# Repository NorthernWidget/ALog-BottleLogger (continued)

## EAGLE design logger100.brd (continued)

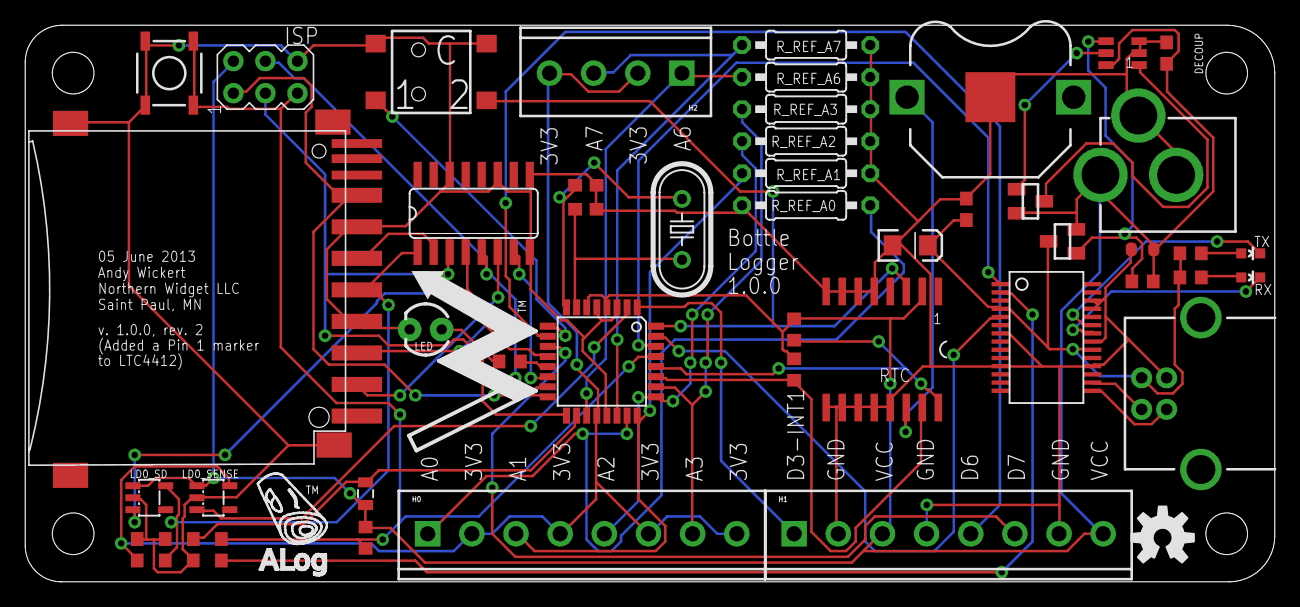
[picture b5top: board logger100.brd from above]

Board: 2 copper layers, 99.0 x 44.1 mm, 54 parts (0 on the bottom side), 46 nets.

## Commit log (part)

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2013-09-11 Create LICENSE.html: CC-BY-SA
2013-09-11 Adding version 0.6.6
2013-09-11 Adding version 1.0.0 files to the master branch
2016-04-27 Next generation: breaking out more pins
2016-04-27 exposed interfaces, button update, board layout
    (1) Exposed SPI, I2C, and UART interfaces
    (2) Added 1K resistors to UART to allow switching away from the computer
    (3) Updated the buttons to PTH (higher button: RESET), PTH DPDT b/c of
    availability (LOG NOW)
    (4) Reworked the board layout to keep the same form factor while adding
    many new screw terminals (and keeping the 3.5 mm spacing)
2016-04-27 Github new standard Eagle-specific
2016-04-27 10nF chip caps for analog, following Gerhard Oberforcher
2016-04-27 a big mess of getting a new FTDI chip
2016-04-28 Added diode OR, not connected yet
2016-04-28 New FTDI chip, power-saving clock circuits (h/t Gerhard), with Chad Sandell
2016-04-28 routed board with clock power-save and new FTDI
2016-04-28 Uniform MOSFETs; diode connection fix
2016-04-29 ALog 1.1 complete
2016-04-29 Improved board, modified and consolidated some components
2016-04-29 Rmv via at screw hole
2016-04-29 Final BoM for ALog 1.1 order
2016-05-07 Return to classic FTDI USB/serial
2016-05-07 Keep a live version of Logger 1.1.0 (new FTDI)
2016-05-17 can not get this to autoroute
2016-05-17 removing the ._## junk eagle files
2016-05-17 Routed board, ground fills and minimized timing device distances
2016-05-18 replace logger with logger_Chad
2016-05-18 remove logger_Chad files, changed to logger
2016-05-20 Added 5V boost from VCC to board
2016-05-24 Route EN pin to tie into 3.3V digital pin (D6 I think)
2016-05-25 5V pin on both sides of board instead of duel ground pins on one side
2016-06-07 Clock power for pull-ups on I2C
2016-06-07 Vcl attached to clock power and communication
2016-06-07 Straighten traces
2016-06-07 Charge pump
2016-06-08 Routed charge pump and gerbers
2016-07-22 Logger2 and logger3, in progress
2016-07-25 fully routed and ready for check
2016-07-28 Updated component packaging
2016-07-28 Updated BOM and board layout with cheaper and smaller component packages
2016-08-01 33pF decoupling on USB data; Rx Tx LED flip
2016-08-09 Fixed misrouted trace
2016-08-09 Update date and version
2016-08-31 Latest design files and board lable fix
2016-09-01 Moved MOSFETs away from clock backup battery
2016-09-16 Final files for V2.0!
2016-09-26 updated schematic layout, added frames
2016-10-06 Added JST connector option to logger, started 2G communication
2016-10-20 BOM additions for ARM chip Alog
2016-10-28 change 3V3 power supply with jumpers, routing needs finishing
2016-10-29 Routed and ready for Wickert check of approval
2016-10-30 Added version number
2016-10-30 Connected VDD to VCL
2016-10-30 Version number visible
2016-10-30 Rerouted with VDD linked to RTC and SD; updated silk labels
2016-10-31 Updates from change to duel 3.3V regulator
2016-10-31 BOM updates from change to duel 3.3V regulator
2016-10-31 removed via under ground pad and fixed 1 airwire
2016-11-23 Old board schematics and diagrams
2016-11-23 Rename folder
2016-11-23 4-page schematic, for publication
2016-11-23 v2.0
2016-11-23 Remove old/other versions
2016-11-23 Logger 2.0 layout, no fill shown, from Eagle
2016-12-20 clean up BOM document
2016-12-20 4412 routing fix and silkscreen gerber fix
2016-12-29 Fix device usage column
2016-12-29 Remove ALog v1.0.0 BoM
2016-12-30 fixed Miso Mosi Silk Screen labels
2017-01-05 Routed new layout, no precision 3V3
2017-01-06 increased pad sizes for 3V3
2017-01-08 Relegating to archive
2017-01-08 5V5 --> 5V
2017-01-09 Create custom pads for 3V3 output voltage chip
2017-01-09 Updated Gerbers
2017-01-22 v2.0-beta silk updates
2017-01-25 Increased pad length for capacitor array
2017-01-30 Switch pins to PWM; need to update software!
2017-01-30 Unnecessary... or at least, so I think.
2017-01-31 Silk
2017-01-31 Silk on proper side
2017-01-31 All pins properly marked; GND plane vias added
2017-01-31 Updated to newer Eagle version
2017-01-31 Safer 5.0V max suggested on silkscreen
2017-01-31 changes to vias
2017-02-04 Smaller back silk -- doesn't overlap through-hole components
2017-02-07 Silk updates for Gerbers
2017-02-07 Remove archives of stored Gerbers
2017-02-07 Old PnP file
2017-02-07 Updated Gerbers: version 2.0.0
2017-02-07 Pick-and-place files
2017-02-08 Visualize the Gerber with gerbv
2017-02-08 Upload to PCB fab house
2017-03-01 Organize silkscreen layers
2017-03-01 Moved 4050 up to increase label visibility, work in progress
2017-03-01 Finished reroute for silk screen label optimization
2017-03-01 Swap swp files
2017-03-08 Simplify I2C pull-ups: no more shorts
2017-03-11 Routed airwires; created larger ground planes
2017-03-11 One more airewire; just TX to go
2017-03-11 SMD LED and Crystal, with I2C pullup short fix
2017-03-11 Silk date update, Route GND, DRC and clearance
2017-03-19 changed pads on capacitor array's, ready for prime time? Check crystal pad.
2017-03-19 chaged pads on 3V3 chip, V2.1.0 ready
2017-03-20 Silkscreen updates
2017-03-21 silk screen updates
2017-03-21 Logo now properly on back silk layer
2017-03-21 Fix logger board outline
2017-03-22 V2.1.0 gerber files
2017-03-22 Gerber update
2017-03-23 SMD USB (micro-B), barrel jack, and battery holder; tentative SMD 1x6 header blocks
2017-03-23 Barrel jack not protruding from board, and fully re-routed
2017-03-31 MOSFET level shifter for SPI, parts for I2C
2017-03-31 All airwires routed; parts for I2C level shifter remain
2017-03-31 Level shifting for I2C
2017-03-31 Rollback to pre-MOSFET-re-addition
2017-04-01 Restore SDA and SCL level shifter; 3V3 output from board
2017-04-01 Note 3V3 SDA, SCL on silk layer
2017-04-07 through hole and surface mount design in progress
2017-04-10 Surface mount reference resistor sockets need to be centered, removing for now
2017-04-10 Removed Surface mount ref resistor headers and changed USB connector
2017-04-10 Updated silk; updates to 'awickert.lbr' messed up voltage switcher
2017-04-10 Fixed accedental change to 4412 chip
2017-05-10 Graphical user's layout for quick reference
2017-05-10 Additional layouts with smaller file sizes
2017-05-11 Larger PNGs: sufficient resolution
2017-05-11 Diagrams, bulletted text
2017-05-11 transparency update
2017-05-11 Data logger unannotated: ALog BottleLogger v2.2.0
2017-05-11 Update to standard image include
2017-05-11 export PNG tweak
2017-05-11 No more shadow of v2.0.0 behind
2017-05-16 changed micro USB to 10118194-0001LF
2017-05-17 lengthened micro USB pads
2017-06-06 empty
2017-06-06 CC-BY-SA 3.0
2017-06-06 Naming consistency with other boards: no longer the only "logger"!
2017-07-01 ALog logo on back silk; no Northern Widget
2017-07-02 Schematic and layout
2017-07-19 Major revision, 1284P 16 channel 16-bit ADC
2017-07-21 Work in progress
2017-07-24 some progress
2017-07-27 more progress
2017-08-01 progress
2017-08-22 latest design files
2017-08-24 4.75 inches long, reference voltages broken out
2017-08-24 fully routed, looking for review
2017-08-24 Add 10K pull downs on mosphets for external controls
2017-08-30 Fixed 5V control and a few other things, fully routed and ready for review
2017-09-05 update gerber files
2017-09-05 add .dri and .gpi files
2017-09-21 Changed cap sizes on 10 and 22 uF to 805 and fixed MISO/MOSI labels on SD card.
2017-09-27 Corrected footprint of 5V regulator
2017-09-29 Changed 3.3 voltage regulator to TPS62172
2017-10-03 latest gerber files, fixes to traces, change to power regulators
2017-10-06 Fixed USB FTDI mosphet connections, updated 3.3V regulator, fixed ground connection on 1.8V reg
2017-10-06 Moved via that blocked 3v3 pin 1 label
2017-10-06 Need to fix DTR connection and remove or isolate ground plane under crystal
2017-10-10 Routed DTR and removed fill planes from under crystal
2017-10-23 COM on ADC should be 2.5V divided from 5V not GND
2017-10-27 improved 3V3 component layout
2017-11-04 Final revisions made, many changes, 5V external mosphet update, RTC power configuration, add 5V psync control pin, change external power control pins, add barrel jack, rerouted whole board
2017-11-07 Straightened wires, very minor edits
2017-11-07 Minor trace fixes, back silkscreen info additions
2017-11-07 Version 3.0.0 gerbers added
2017-11-13 ordered for AGU meeting
2017-11-30 Updated part data
2017-12-20 Added comparators, added SCL/SDA connections, updated resistor values and voltage divider sources
2017-12-20 EXT_5V on COM voltage divider on ADC
2017-12-28 Add comparators for power control, change header layout adding more I2C, change clock power supply
2017-12-29 update botton pad sizes
2018-06-17 CC-BY-SA
2018-06-17 CC-BY-SA 3.0 --> 4.0
2018-09-14 Cleanup and PDF creation
    Cleaned up and updated old parts, added frames to schematic, printed schematic to PDF
2019-01-12 updated BoM for DigiKey stocks
2021-03-02 Modern logger links
